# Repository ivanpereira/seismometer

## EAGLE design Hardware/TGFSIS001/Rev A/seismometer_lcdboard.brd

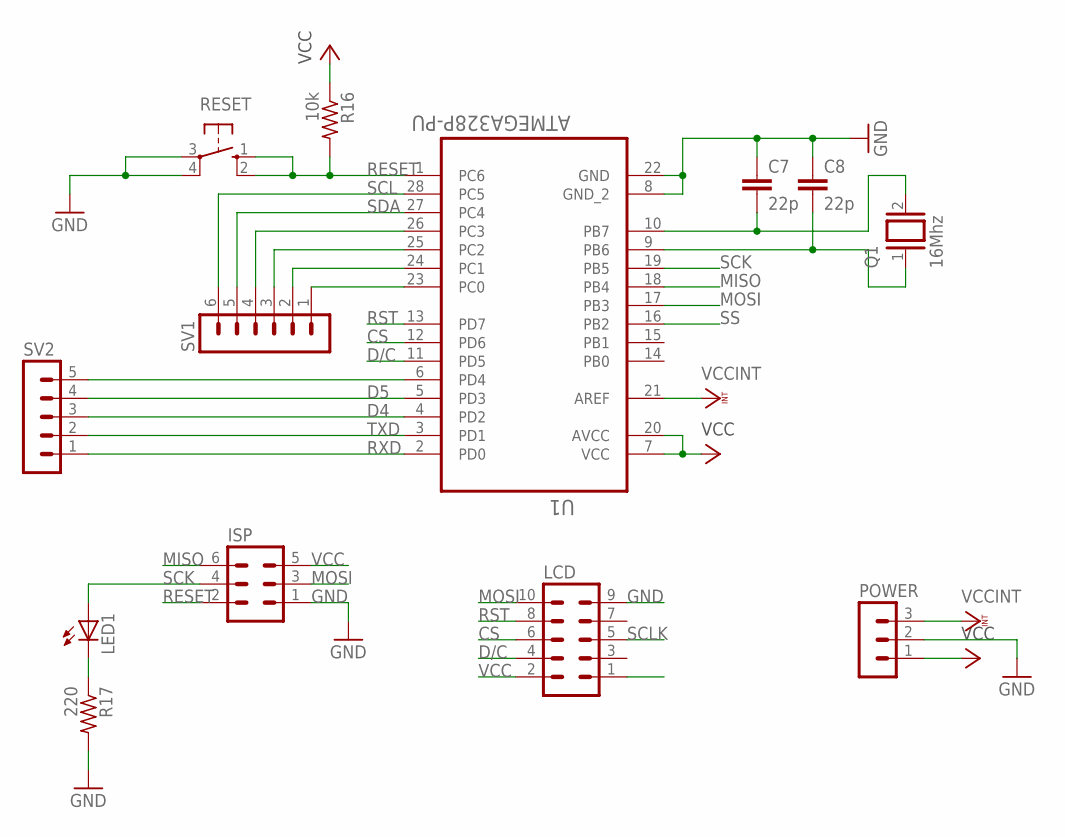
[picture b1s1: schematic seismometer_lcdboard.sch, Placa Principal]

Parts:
C7, C8: 22p; C050-025X075
ISP: MA03-2
LCD: MA05-2
LED1: LED3MM
POWER: MA03-1
Q1: 16Mhz; QS
R16: 10k; 0207/12
R17: 220; 0207/12
RESET: 10-XX; B3F-10XX
SV1: MA06-1
SV2: MA05-1
U1: ATMEGA328P-PU; DIP254P762X457-28

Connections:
CS: LCD.6, U1.12 (PD6)
D4: SV2.3, U1.4 (PD2)
D5: SV2.4, U1.5 (PD3)
D/C: LCD.4, U1.11 (PD5)
GND: C7.1, C8.1, ISP.1, LCD.9, POWER.2, R17.2, RESET.3, RESET.4 (P1), U1.8 (GND_2), U1.22 (GND)
MISO: ISP.6, U1.18 (PB4)
MOSI: ISP.3, LCD.10, U1.17 (PB3)
unnamed: SV1.1, U1.23 (PC0)
unnamed: SV1.2, U1.24 (PC1)
unnamed: SV1.3, U1.25 (PC2)
unnamed: SV1.4, U1.26 (PC3)
unnamed: SV2.5, U1.6 (PD4)
unnamed: C7.2, Q1.2, U1.10 (PB7)
unnamed: C8.2, Q1.1, U1.9 (PB6)
unnamed: LED1.K (C), R17.1
RESET: ISP.2, R16.2, RESET.1 (S), RESET.2 (S1), U1.1 (PC6)
RST: LCD.8, U1.13 (PD7)
RXD: SV2.1, U1.2 (PD0)
SCK: ISP.4, LED1.A, U1.19 (PB5)
SCL: SV1.6, U1.28 (PC5)
SCLK: LCD.5
SDA: SV1.5, U1.27 (PC4)
SS: U1.16 (PB2)
TXD: SV2.2, U1.3 (PD1)
VCC: ISP.5, LCD.2, POWER.1, R16.1, U1.7 (VCC), U1.20 (AVCC)
VCCINT: POWER.3, U1.21 (AREF)

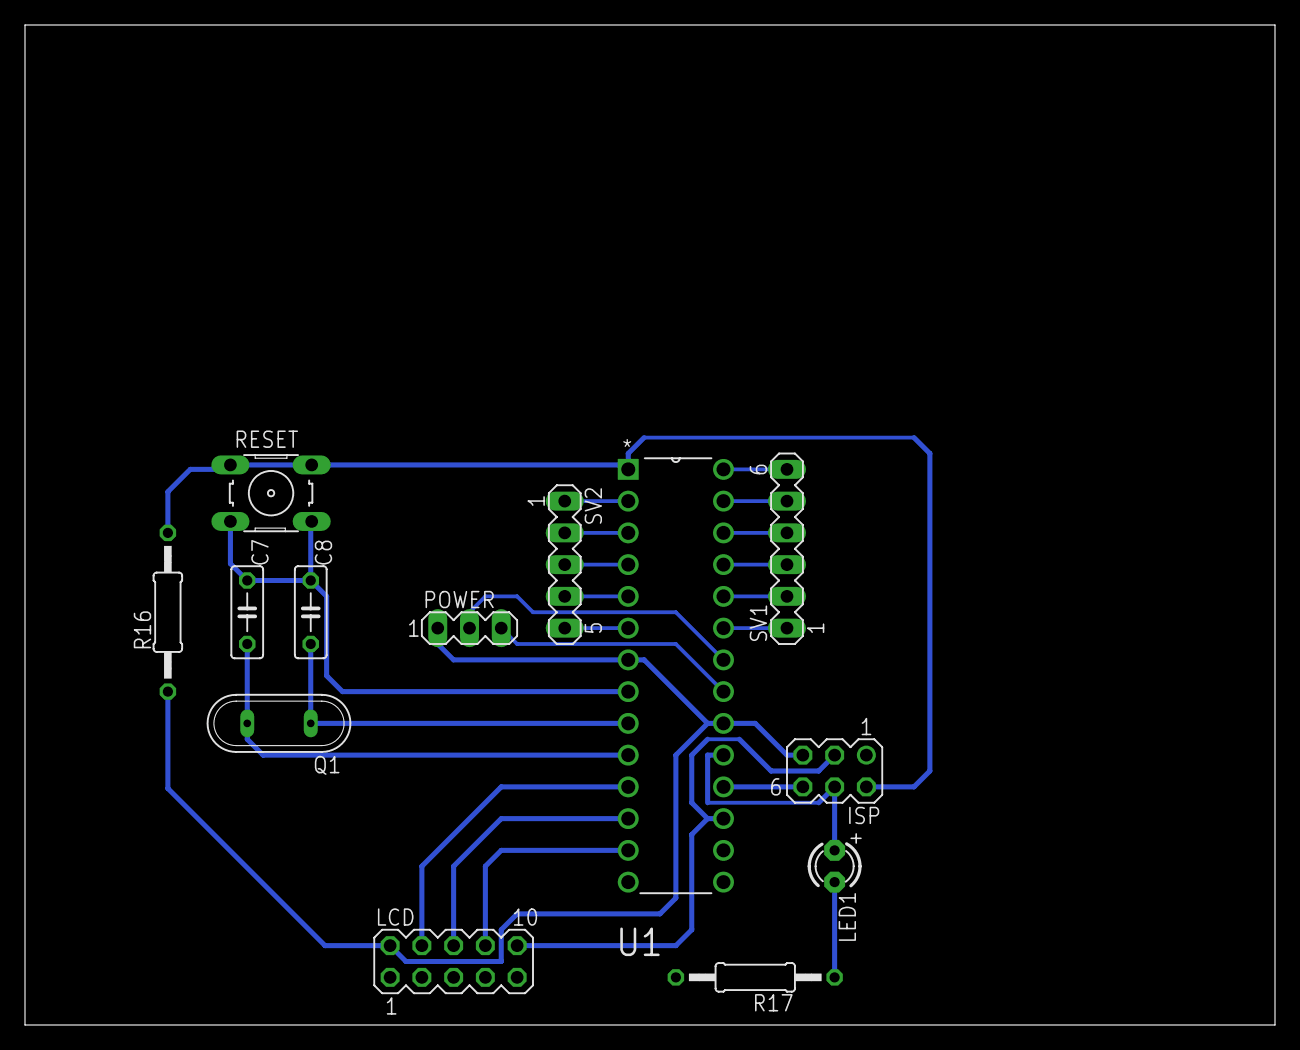
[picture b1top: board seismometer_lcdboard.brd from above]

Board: 2 copper layers, 100.0 x 80.0 mm, 13 parts (0 on the bottom side), 24 nets.

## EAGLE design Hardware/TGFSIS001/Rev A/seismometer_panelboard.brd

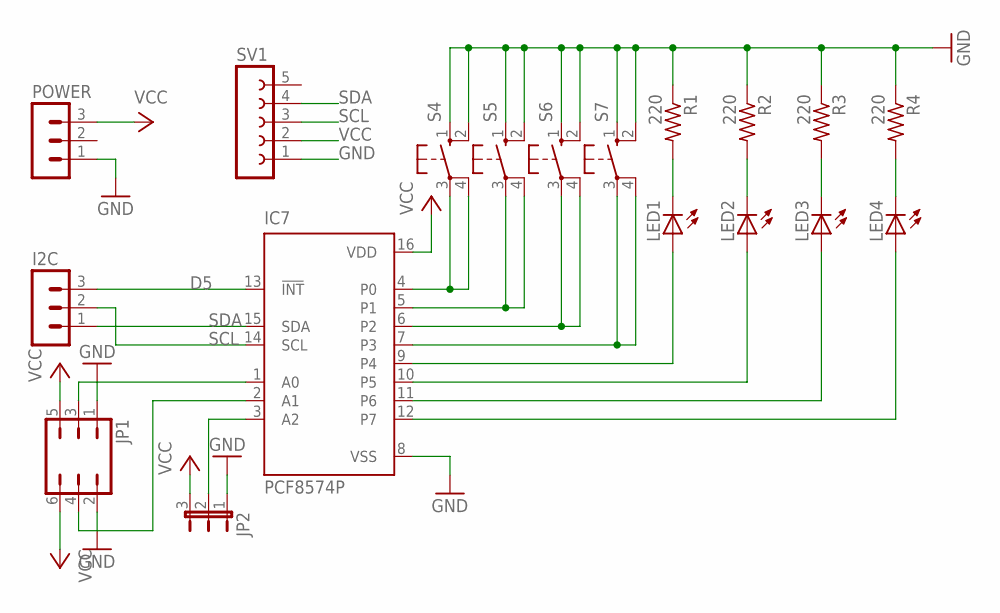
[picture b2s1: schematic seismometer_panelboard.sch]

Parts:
I2C: MA03-1
IC7: PCF8574P; DIL16
JP1: JP3Q
JP2: JP2E; JP2
LED1, LED2, LED3, LED4: LED3MM
POWER: MA03-1
R1, R2, R3, R4: 220; 0207/10
S4, S5, S6, S7: 10-XX; B3F-10XX
SV1: FE05-1

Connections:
D5: I2C.3, IC7.13 (!INT)
GND: IC7.8 (VSS), JP1.1, JP1.2, JP2.1, POWER.1, R1.1, R2.1, R3.1, R4.1, S4.1 (S), S4.2 (S1), S5.1 (S), S5.2 (S1), S6.1 (S), S6.2 (S1), S7.1 (S), S7.2 (S1), SV1.1
unnamed: IC7.9 (P4), LED1.A
unnamed: IC7.10 (P5), LED2.A
unnamed: IC7.11 (P6), LED3.A
unnamed: IC7.12 (P7), LED4.A
unnamed: LED1.K (C), R1.2
unnamed: LED2.K (C), R2.2
unnamed: LED3.K (C), R3.2
unnamed: LED4.K (C), R4.2
unnamed: IC7.1 (A0), JP1.3
unnamed: IC7.2 (A1), JP1.4
unnamed: IC7.3 (A2), JP2.2
unnamed: IC7.4 (P0), S4.3, S4.4 (P1)
unnamed: IC7.6 (P2), S6.3, S6.4 (P1)
unnamed: IC7.7 (P3), S7.3, S7.4 (P1)
unnamed: IC7.5 (P1), S5.3, S5.4 (P1)
SCL: I2C.2, IC7.14 (SCL), SV1.3
SDA: I2C.1, IC7.15 (SDA), SV1.4
VCC: IC7.16 (VDD), JP1.5, JP1.6, JP2.3, POWER.3, SV1.2

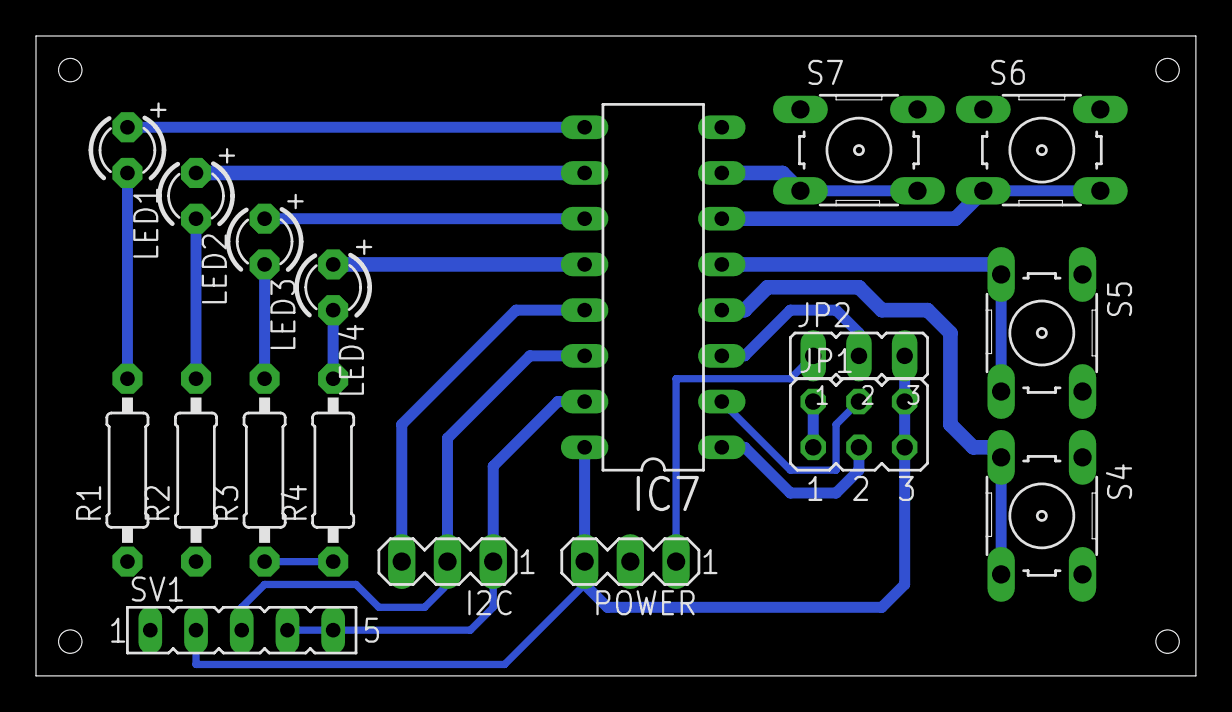
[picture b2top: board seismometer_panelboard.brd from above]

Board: 2 copper layers, 64.4 x 35.5 mm, 18 parts (0 on the bottom side), 20 nets.

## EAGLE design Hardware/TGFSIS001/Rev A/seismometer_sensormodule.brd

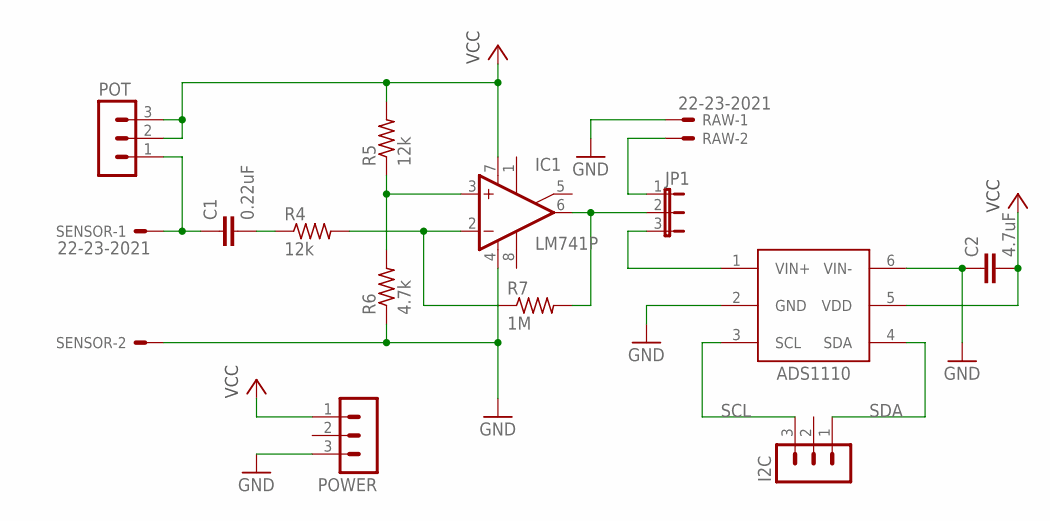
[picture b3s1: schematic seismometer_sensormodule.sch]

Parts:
C1: 0.22uF; C025-030X050
C2: 4.7uF; C025-030X050
I2C: MA03-1
IC1: LM741P; DIL08
IC2: ADS1110; SOT-23-6
JP1: JP2E; JP2
POT: MA03-1
POWER: MA03-1
R4, R5: 12k; 0207/12
R6: 4.7k; 0207/12
R7: 1M; 0207/12
RAW: 22-23-2021
SENSOR: 22-23-2021

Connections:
GND: C2.1, IC1.4 (V-), IC2.2 (GND), IC2.6 (VIN-), POWER.3, R6.1, RAW.1, SENSOR.2
unnamed: IC2.1 (VIN+), JP1.3
unnamed: C1.2, R4.1
unnamed: IC1.2 (-IN), R4.2, R7.1
unnamed: JP1.1, RAW.2
unnamed: IC1.3 (+IN), R5.1, R6.2
unnamed: C1.1, POT.1, SENSOR.1
unnamed: IC1.6 (OUT), JP1.2, R7.2
SCL: I2C.3, IC2.3 (SCL)
SDA: I2C.1, IC2.4 (SDA)
VCC: C2.2, IC1.7 (V+), IC2.5 (VDD), POT.2, POT.3, POWER.1, R5.2

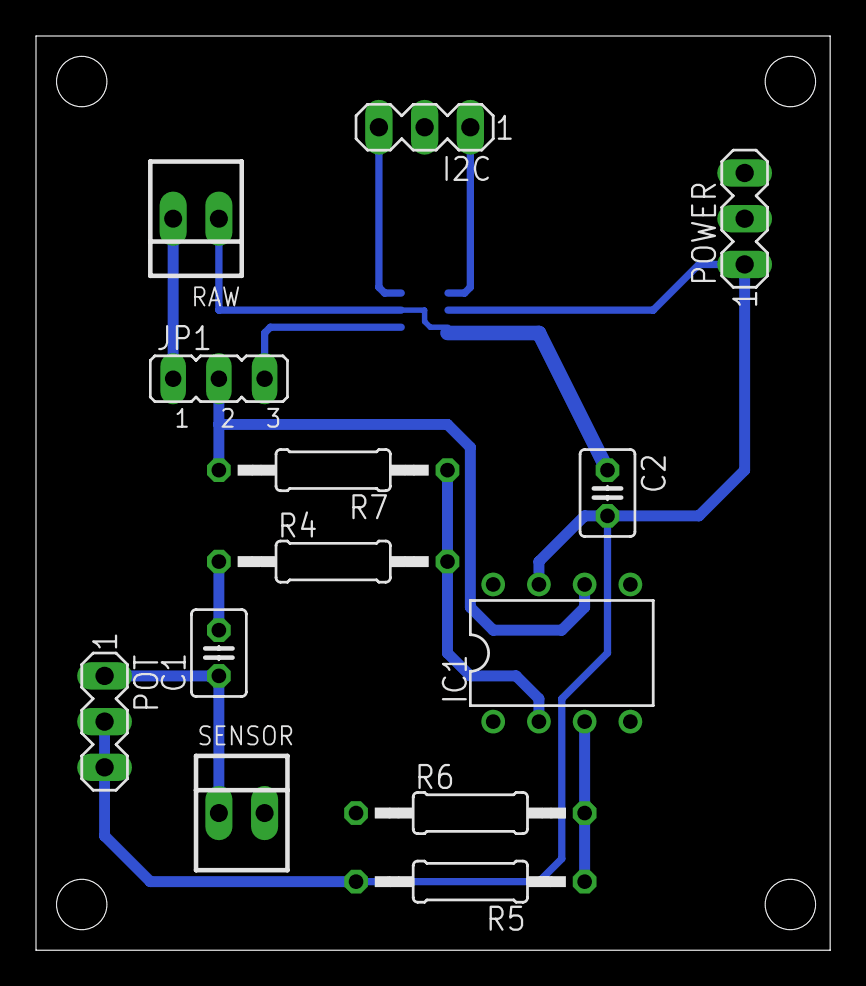
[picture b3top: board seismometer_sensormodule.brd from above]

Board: 2 copper layers, 44.1 x 50.8 mm, 14 parts (1 on the bottom side), 11 nets.

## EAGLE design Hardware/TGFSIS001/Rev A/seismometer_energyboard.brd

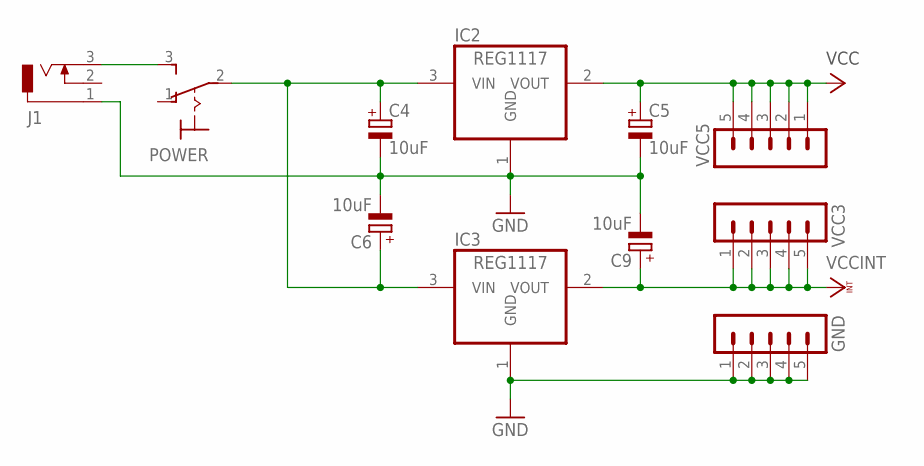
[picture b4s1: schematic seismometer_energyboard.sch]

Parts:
C4, C5, C6, C9: 10uF; E2,5-6
GND: MA05-1
IC2, IC3: REG1117; SOT223
J1: DCJ0303
POWER: 320-916
VCC3, VCC5: MA05-1

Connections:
GND: C4.-, C5.-, C6.-, C9.-, GND.1, GND.2, GND.3, GND.4, GND.5, IC2.1 (GND), IC3.1 (GND), J1.1
unnamed: C4.+, C6.+, IC2.3 (VIN), IC3.3 (VIN), POWER.2
unnamed: J1.3, POWER.3 (S)
VCC: C5.+, IC2.2 (VOUT), VCC5.1, VCC5.2, VCC5.3, VCC5.4, VCC5.5
VCCINT: C9.+, IC3.2 (VOUT), VCC3.1, VCC3.2, VCC3.3, VCC3.4, VCC3.5

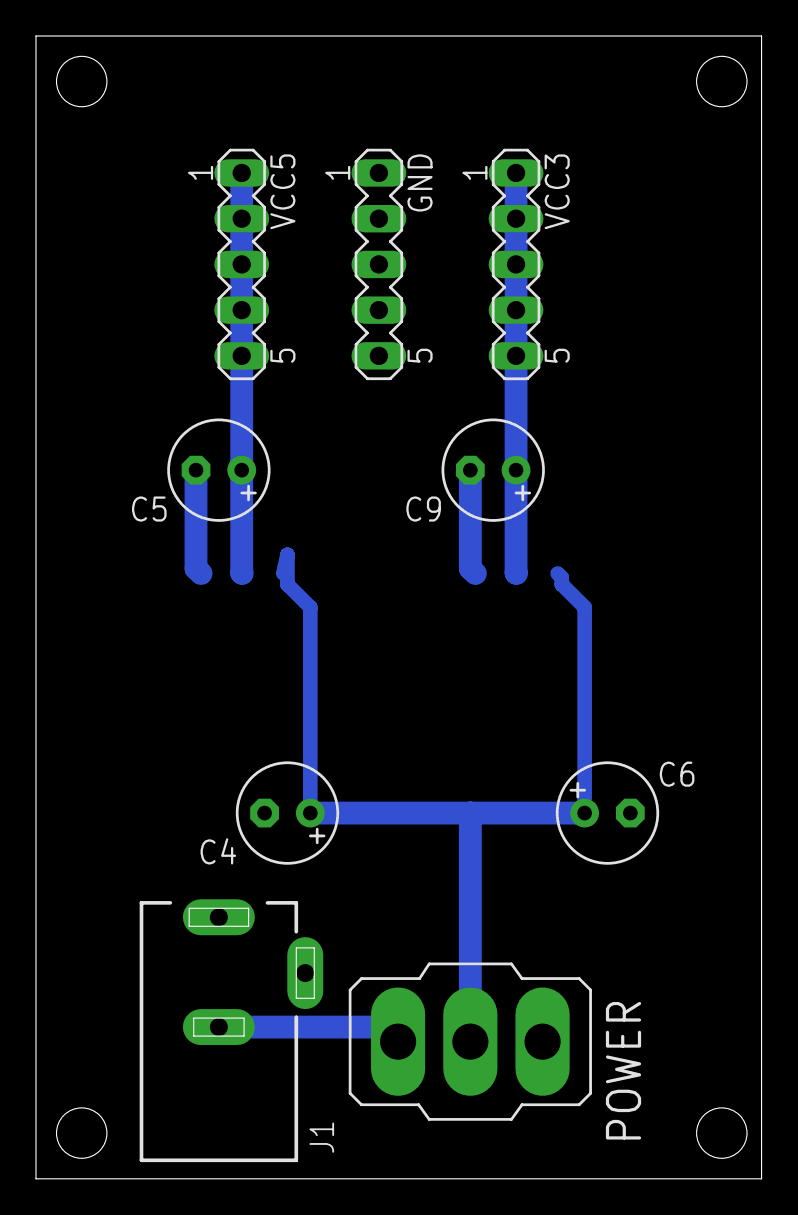
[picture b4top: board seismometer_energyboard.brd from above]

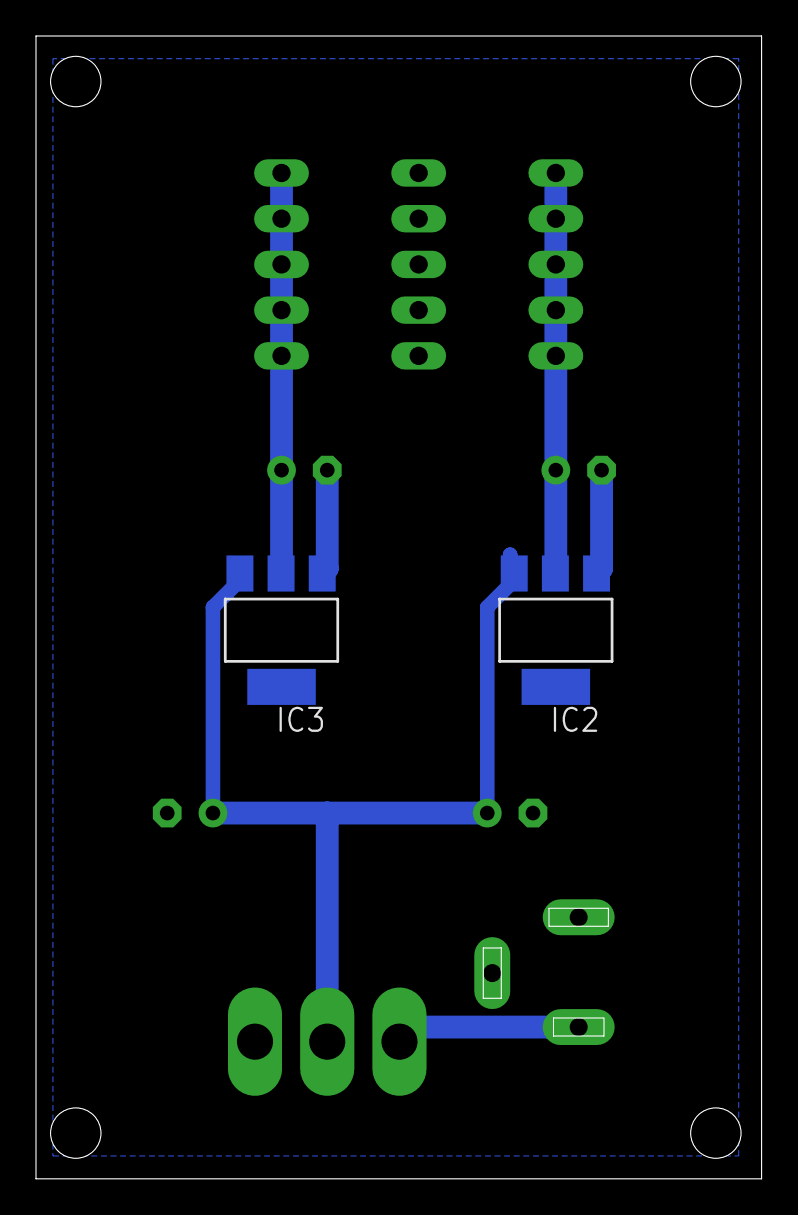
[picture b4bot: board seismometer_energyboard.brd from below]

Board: 2 copper layers, 40.3 x 63.5 mm, 11 parts (2 on the bottom side), 5 nets.

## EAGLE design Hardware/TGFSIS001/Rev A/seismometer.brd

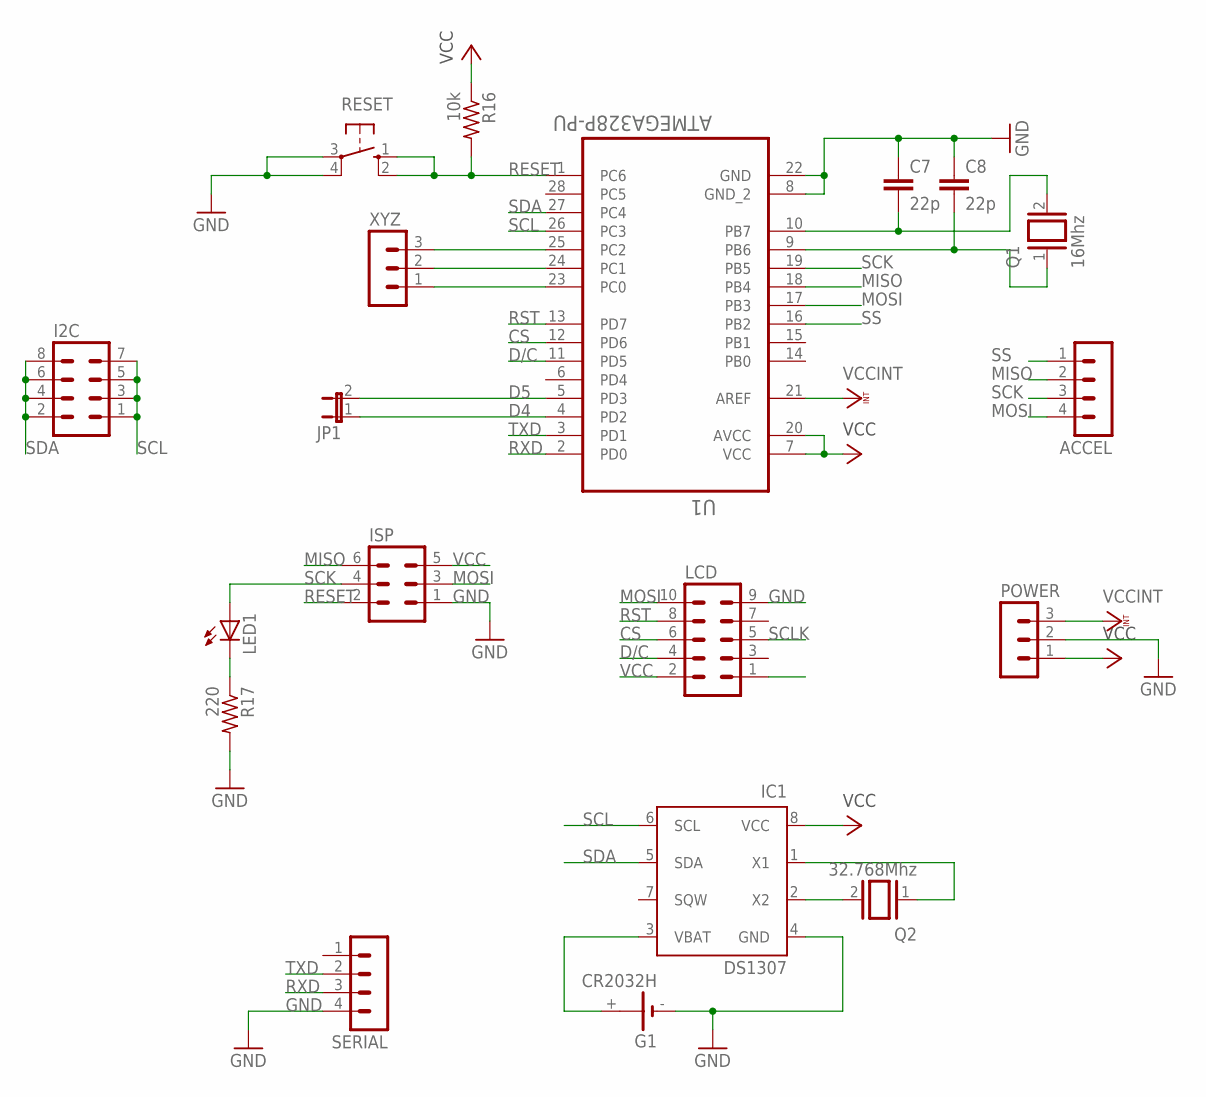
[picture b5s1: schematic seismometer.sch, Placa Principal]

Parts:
ACCEL: MA04-1
C7, C8: 22p; C050-025X075
G1: CR2032H
I2C: MA04-2
IC1: DS1307; DIL08
ISP: MA03-2
JP1: JP1E; JP1
LCD: MA05-2
LED1: LED3MM
POWER: MA03-1
Q1: 16Mhz; QS
Q2: 32.768Mhz; QS
R16: 10k; 0207/12
R17: 220; 0207/12
RESET: 10-XX; B3F-10XX
SERIAL: MA04-1
U1: ATMEGA328P-PU; DIP254P762X457-28
XYZ: MA03-1

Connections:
CS: LCD.6, U1.12 (PD6)
D4: JP1.1, U1.4 (PD2)
D5: JP1.2, U1.5 (PD3)
D/C: LCD.4, U1.11 (PD5)
GND: C7.1, C8.1, G1.-, IC1.4 (GND), ISP.1, LCD.9, POWER.2, R17.2, RESET.3, RESET.4 (P1), SERIAL.4, U1.8 (GND_2), U1.22 (GND)
MISO: ACCEL.2, ISP.6, U1.18 (PB4)
MOSI: ACCEL.4, ISP.3, LCD.10, U1.17 (PB3)
unnamed: U1.23 (PC0), XYZ.1
unnamed: U1.24 (PC1), XYZ.2
unnamed: U1.25 (PC2), XYZ.3
unnamed: C7.2, Q1.2, U1.10 (PB7)
unnamed: C8.2, Q1.1, U1.9 (PB6)
unnamed: IC1.1 (X1), Q2.1
unnamed: IC1.2 (X2), Q2.2
unnamed: G1.+, IC1.3 (VBAT)
unnamed: LED1.K (C), R17.1
RESET: ISP.2, R16.2, RESET.1 (S), RESET.2 (S1), U1.1 (PC6)
RST: LCD.8, U1.13 (PD7)
RXD: SERIAL.3, U1.2 (PD0)
SCK: ACCEL.3, ISP.4, LED1.A, U1.19 (PB5)
SCL: I2C.1, I2C.3, I2C.5, I2C.7, IC1.6 (SCL), U1.26 (PC3)
SCLK: LCD.5
SDA: I2C.2, I2C.4, I2C.6, I2C.8, IC1.5 (SDA), U1.27 (PC4)
SS: ACCEL.1, U1.16 (PB2)
TXD: SERIAL.2, U1.3 (PD1)
VCC: IC1.8 (VCC), ISP.5, LCD.2, POWER.1, R16.1, U1.7 (VCC), U1.20 (AVCC)
VCCINT: POWER.3, U1.21 (AREF)

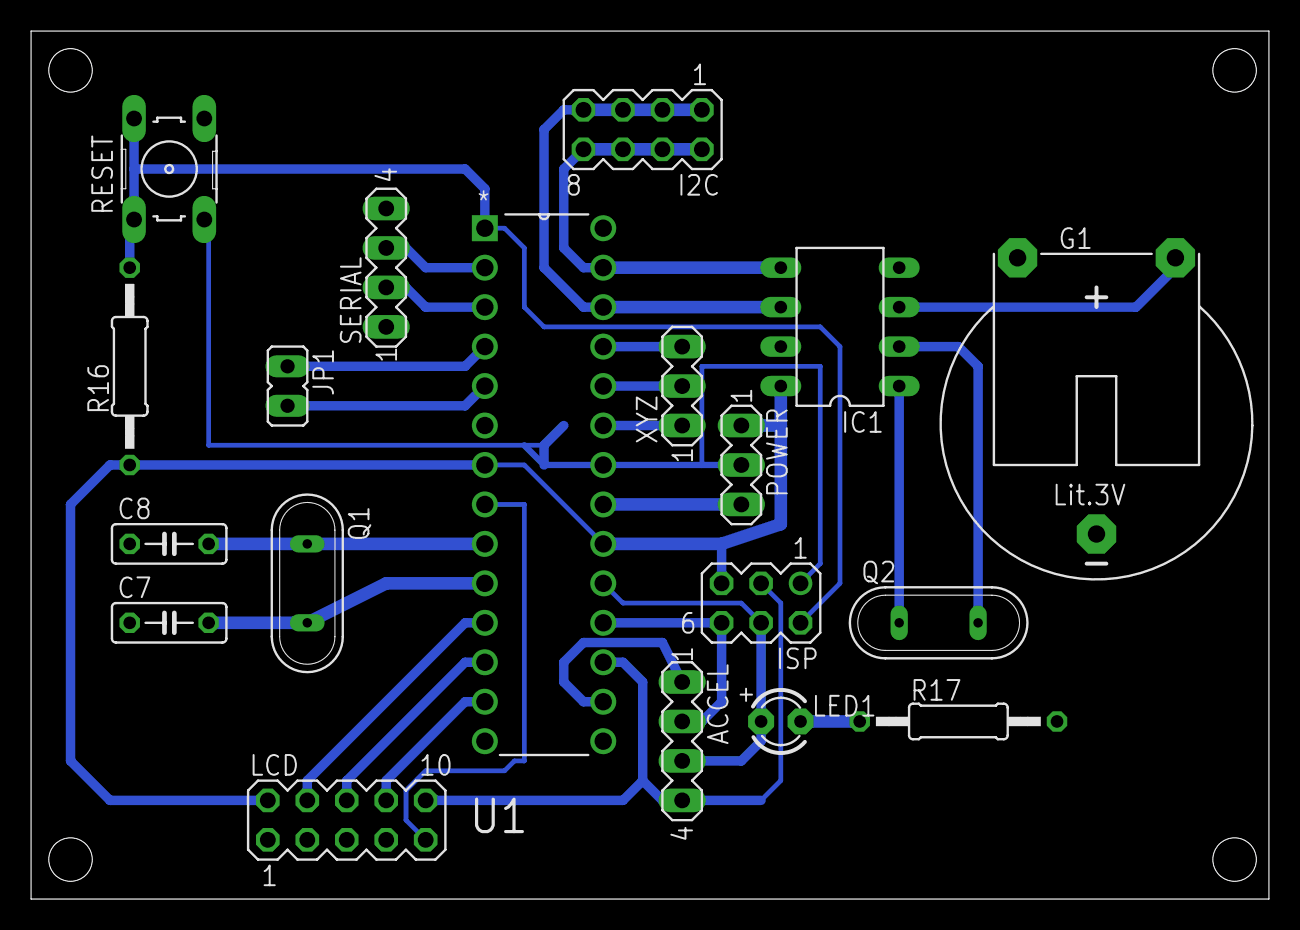
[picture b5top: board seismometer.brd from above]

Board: 2 copper layers, 79.7 x 55.9 mm, 19 parts (0 on the bottom side), 26 nets.

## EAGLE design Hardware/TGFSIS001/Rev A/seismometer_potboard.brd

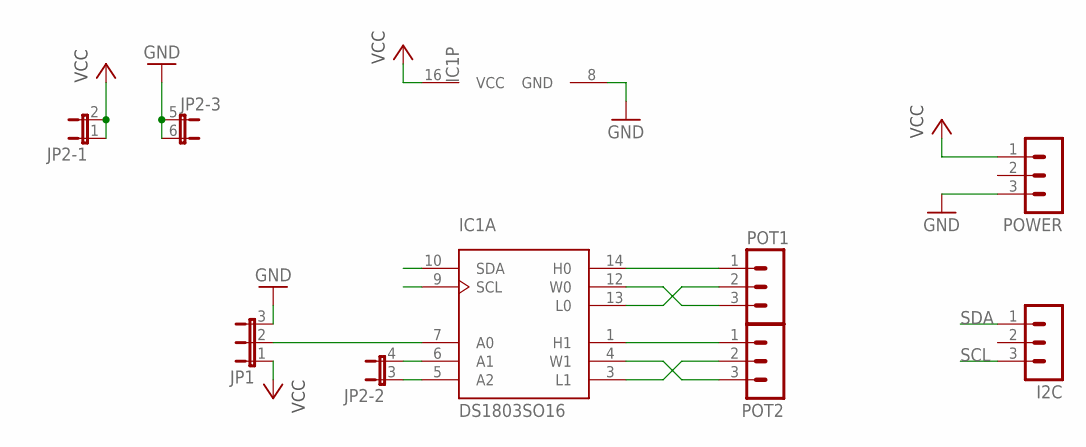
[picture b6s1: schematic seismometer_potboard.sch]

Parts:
I2C: MA03-1
IC1: DS1803SO16; SO16
JP1: JP2E; JP2
JP2: JP3QE; JP3Q
POT1, POT2: MA03-1
POWER: MA03-1

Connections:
GND: IC1.8 (GND), JP1.3, JP2.5 (1), JP2.6 (2), POWER.3
unnamed: IC1.5 (A2), JP2.3 (1)
unnamed: IC1.6 (A1), JP2.4 (2)
unnamed: IC1.7 (A0), JP1.2
unnamed: IC1.14 (H0), POT1.1
unnamed: IC1.13 (L0), POT1.2
unnamed: IC1.12 (W0), POT1.3
unnamed: IC1.1 (H1), POT2.1
unnamed: IC1.3 (L1), POT2.2
unnamed: IC1.4 (W1), POT2.3
SCL: I2C.3, IC1.9 (SCL)
SDA: I2C.1, IC1.10 (SDA)
VCC: IC1.16 (VCC), JP1.1, JP2.1, JP2.2, POWER.1

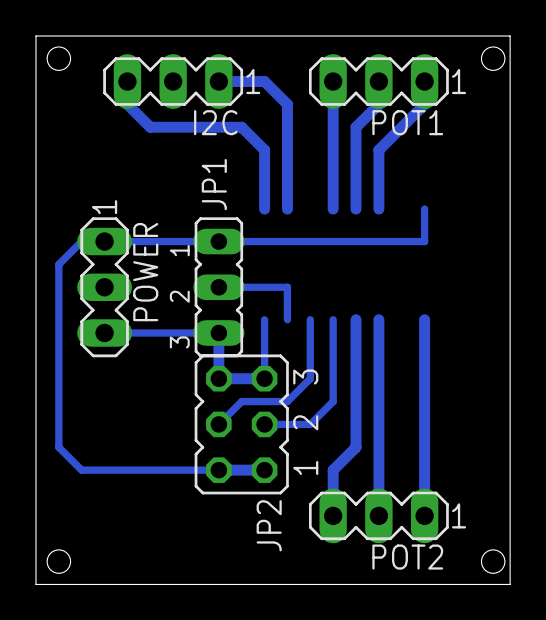
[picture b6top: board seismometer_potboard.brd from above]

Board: 2 copper layers, 26.3 x 30.5 mm, 7 parts (1 on the bottom side), 13 nets.

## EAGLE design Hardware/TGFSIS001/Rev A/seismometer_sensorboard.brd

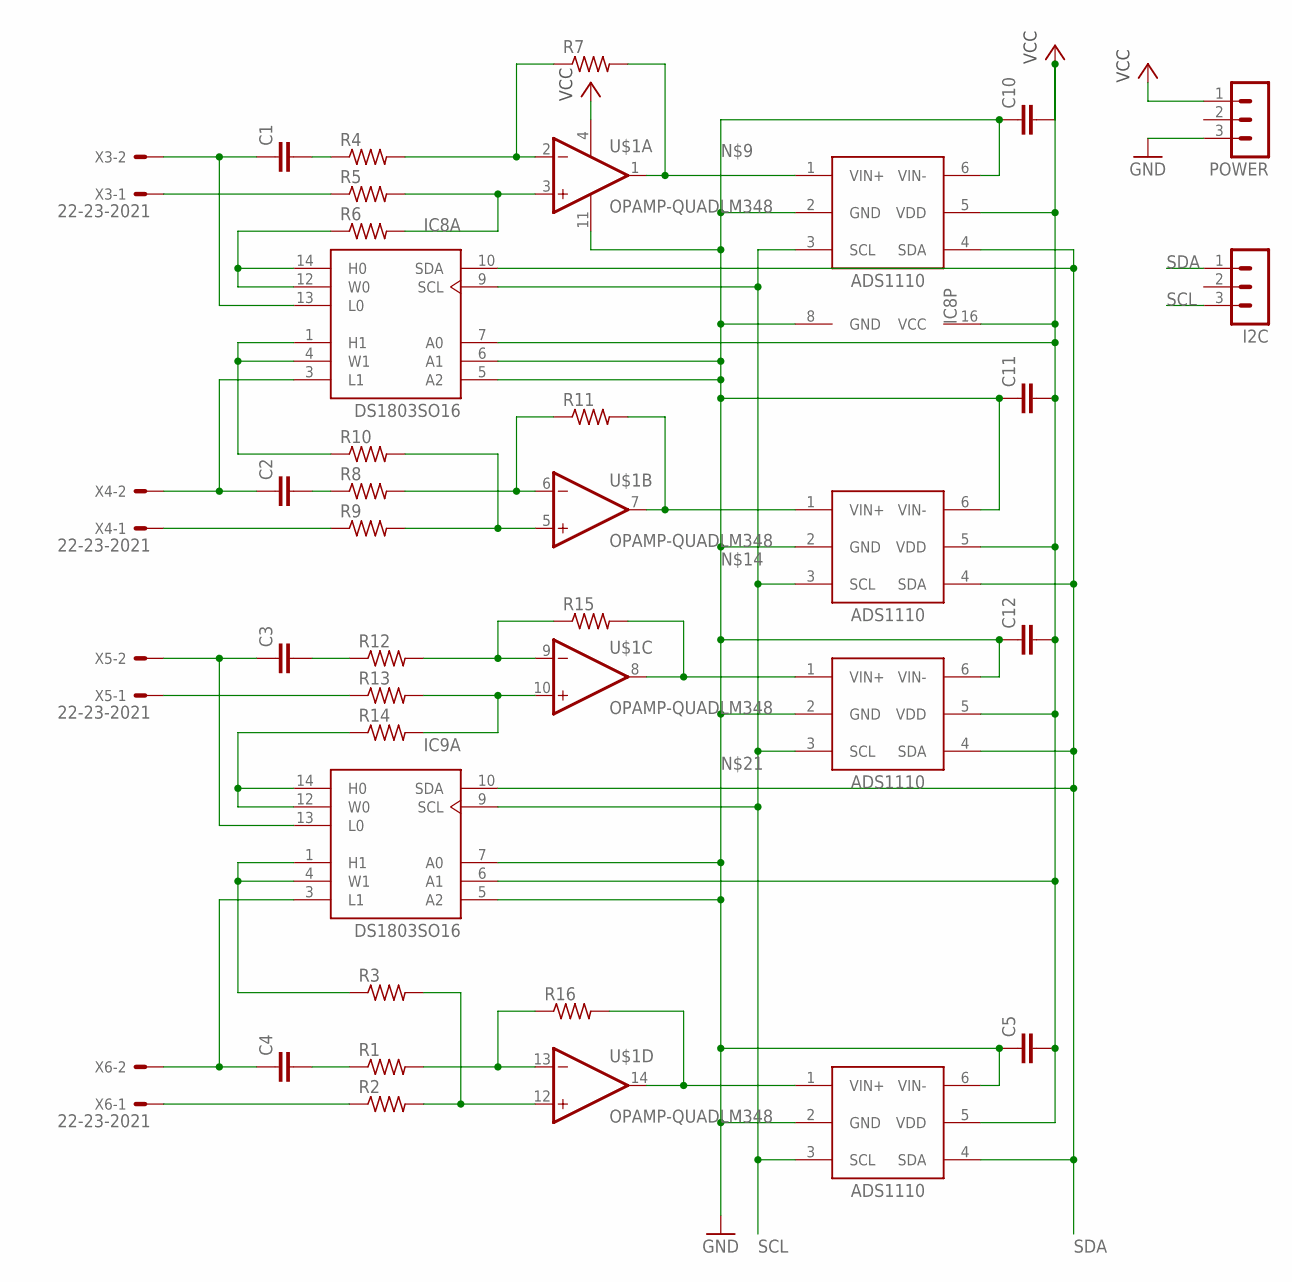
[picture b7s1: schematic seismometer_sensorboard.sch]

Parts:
C1, C2, C3, C4, C5, C10, C11, C12: C-EU025-030X050; C025-030X050
I2C: MA03-1
IC1, IC4, IC5, IC6: ADS1110; SOT-23-6
IC8, IC9: DS1803SO16; SO16
POWER: MA03-1
R1, R2, R3, R4, R5, R6, R7, R8, R9, R10, R11, R12, R13, R14, R15, R16: R-US_0207/12; 0207/12
U$1: OPAMP-QUADLM348; DIP14
X3, X4, X5, X6: 22-23-2021

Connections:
GND: C5.1, C10.1, C11.1, C12.1, IC1.2 (GND), IC1.6 (VIN-), IC4.2 (GND), IC4.6 (VIN-), IC5.2 (GND), IC5.6 (VIN-), IC6.2 (GND), IC6.6 (VIN-), IC8.5 (A2), IC8.6 (A1), IC8.8 (GND), IC9.5 (A2), IC9.7 (A0), IC9.8 (GND), POWER.3, U$1.11 (VEE)
unnamed: C1.1, IC8.13 (L0), X3.2
unnamed: C1.2, R4.1
unnamed: R5.1, X3.1
unnamed: C2.1, IC8.3 (L1), X4.2
unnamed: R4.2, R7.1, U$1.2 (IN-)
unnamed: R5.2, R6.2, U$1.3 (IN+)
unnamed: IC8.1 (H1), IC8.4 (W1), R10.1
unnamed: IC4.1 (VIN+), R7.2, U$1.1 (OUT)
unnamed: R9.1, X4.1
unnamed: C2.2, R8.1
unnamed: R9.2, R10.2, U$1.5 (IN+)
unnamed: R8.2, R11.1, U$1.6 (IN-)
unnamed: IC5.1 (VIN+), R11.2, U$1.7 (OUT)
unnamed: C3.1, IC9.13 (L0), X5.2
unnamed: C4.1, IC9.3 (L1), X6.2
unnamed: R13.1, X5.1
unnamed: R13.2, R14.2, U$1.10 (IN+)
unnamed: R12.2, R15.1, U$1.9 (IN-)
unnamed: C3.2, R12.1
unnamed: IC6.1 (VIN+), R15.2, U$1.8 (OUT)
unnamed: C4.2, R1.1
unnamed: R2.1, X6.1
unnamed: IC8.12 (W0), IC8.14 (H0), R6.1
unnamed: IC9.1 (H1), IC9.4 (W1), R3.1
unnamed: R2.2, R3.2, U$1.12 (IN+)
unnamed: R1.2, R16.1, U$1.13 (IN-)
unnamed: IC1.1 (VIN+), R16.2, U$1.14 (OUT)
unnamed: IC9.12 (W0), IC9.14 (H0), R14.1
SCL: I2C.3, IC1.3 (SCL), IC4.3 (SCL), IC5.3 (SCL), IC6.3 (SCL), IC8.9 (SCL), IC9.9 (SCL)
SDA: I2C.1, IC1.4 (SDA), IC4.4 (SDA), IC5.4 (SDA), IC6.4 (SDA), IC8.10 (SDA), IC9.10 (SDA)
VCC: C5.2, C10.2, C11.2, C12.2, IC1.5 (VDD), IC4.5 (VDD), IC5.5 (VDD), IC6.5 (VDD), IC8.7 (A0), IC8.16 (VCC), IC9.6 (A1), IC9.16 (VCC), POWER.1, U$1.4 (VCC)

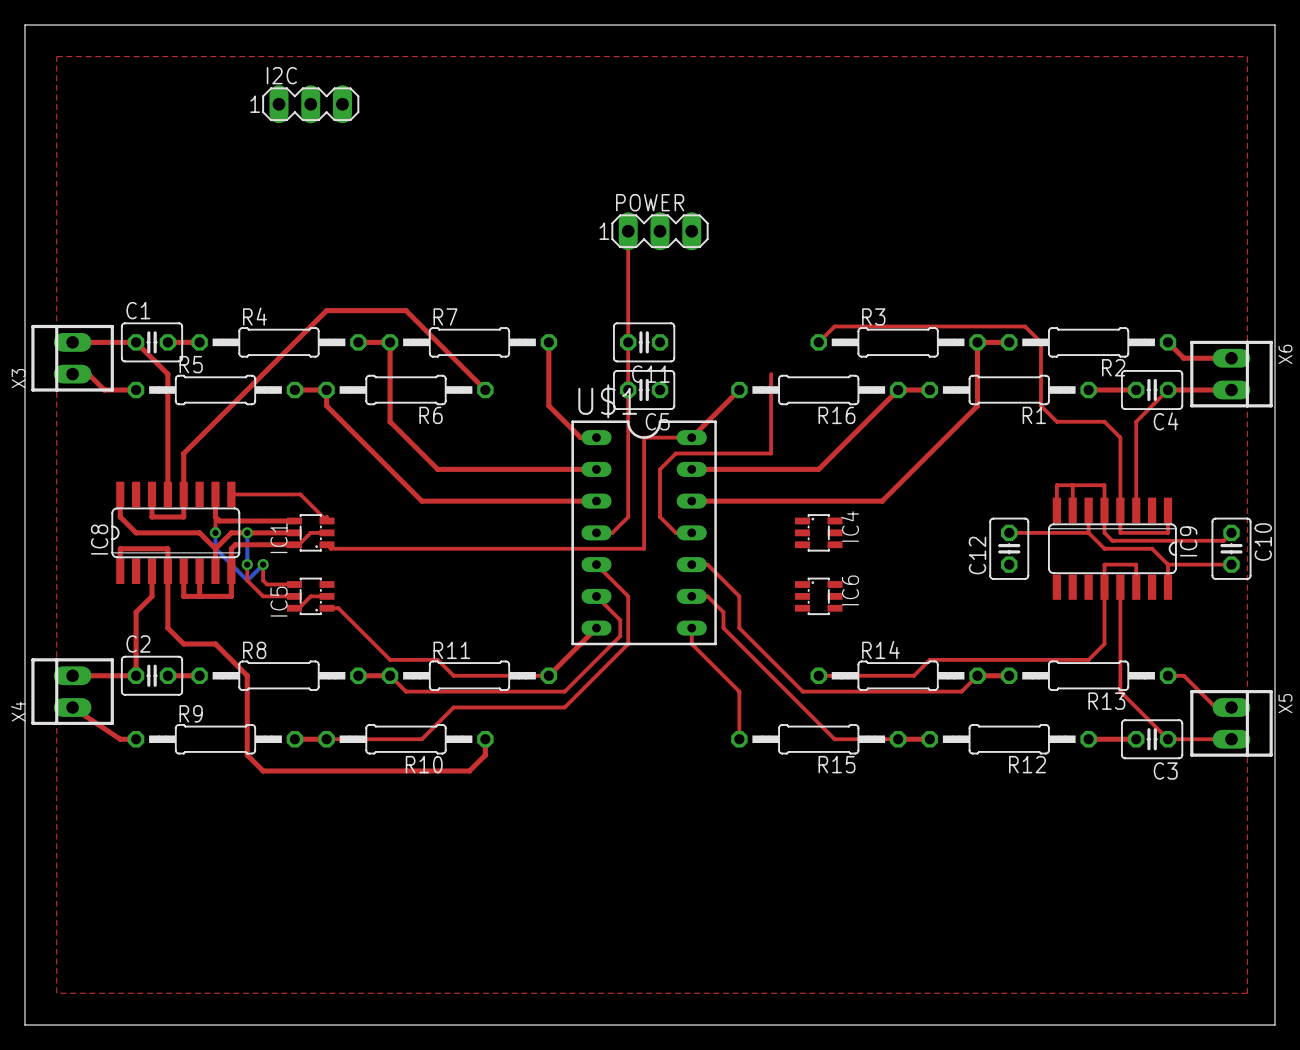
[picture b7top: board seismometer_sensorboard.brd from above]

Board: 2 copper layers, 100.0 x 80.0 mm, 37 parts (0 on the bottom side), 32 nets.

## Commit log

2015-02-17 Eagle Files
    First hardware files
